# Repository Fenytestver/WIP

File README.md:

# Sump Pit Sensor & Remote monitoring

## Overview
to stop tracking local onfiguration files, run this git command in SumpPitSensorProject/src/:
git update-index --skip-worktree localsettings.h

## Project structure

SumpPitSensorProject	// project root
	lib					// libraries
		sumppitmodel	// main business logic implementation
	src					// main, runnable files
	test				// test code
## Links
http://particle.io - Particle.io

http://bitbucket.com - Version control (git)

https://www.sourcetreeapp.com/ - Win/Mac client for Git

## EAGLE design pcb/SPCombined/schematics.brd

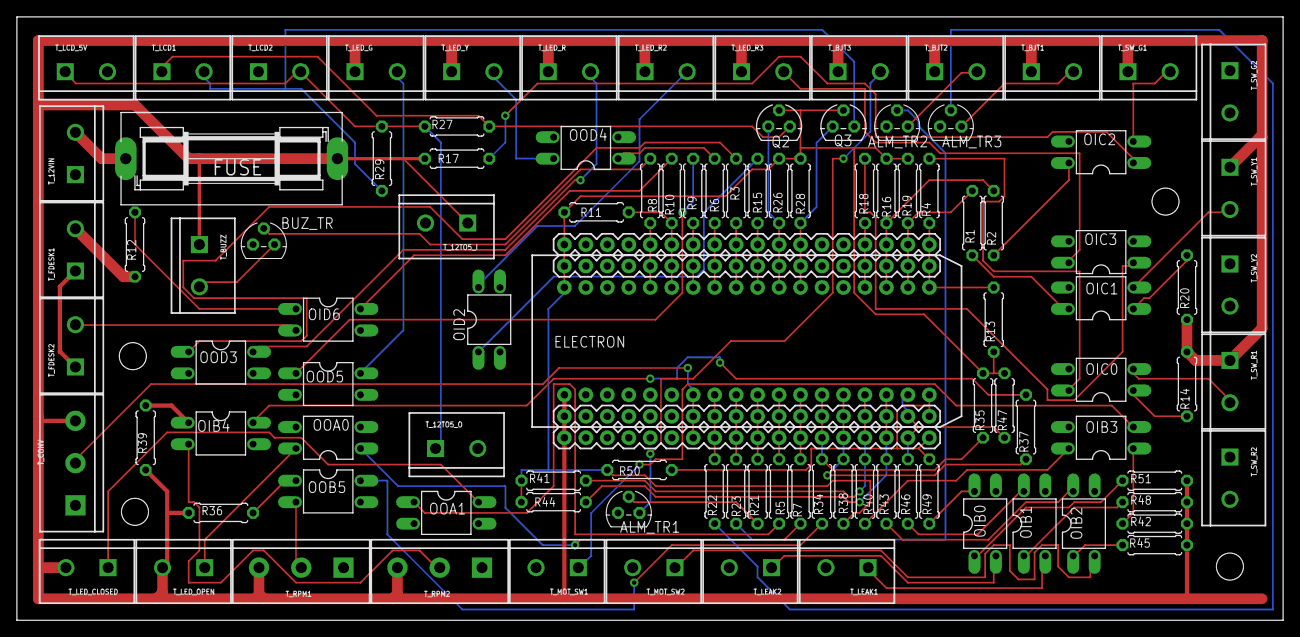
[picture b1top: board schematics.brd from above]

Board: 2 copper layers, 149.8 x 71.4 mm, 102 parts (0 on the bottom side), 85 nets.

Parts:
ALM_TR1, ALM_TR2, ALM_TR3: 2N3904; TO92
BUZ_TR: 2N3904; TO92
ELECTRON: ELECTRONDUALROW; ELECTRON_DUAL-ROW
FUSE: SH25
OIB0, OIB1, OIB2, OIB3, OIB4: PC817; DIL04
OIC0, OIC1, OIC2, OIC3: PC817; DIL04
OID2, OID6: PC817; DIL04
OOA0, OOA1: PC817; DIL04
OOB5: PC817; DIL04
OOD3, OOD4, OOD5: PC817; DIL04
Q2, Q3: TO-92
R1, R2, R3, R4, R5, R6, R7, R9, R10, R15, R18, R34, R37, R40, R43, R46, R49: 220; 0207/7
R8, R21, R22, R23: 2.2k; 0207/7
R11, R13, R16, R19, R26, R27, R28, R29, R35, R38, R41, R44, R47, R50: 10k; 0207/7
R12, R14, R17, R20, R36, R39, R42, R45, R48, R51: 1k; 0207/7
T_12TO5_I, T_12TO5_O, T_12VIN: SCREWTERMINAL-5MM-2
T_BJT1, T_BJT2, T_BJT3: SCREWTERMINAL-5MM-2
T_BUZZ: SCREWTERMINAL-5MM-2
T_CONV: SCREWTERMINAL-5MM-3
T_FDESK1, T_FDESK2: SCREWTERMINAL-5MM-2
T_LCD1, T_LCD2: SCREWTERMINAL-5MM-2
T_LCD_5V: SCREWTERMINAL-5MM-2
T_LEAK1, T_LEAK2: SCREWTERMINAL-5MM-2
T_LED_CLOSED: SCREWTERMINAL-5MM-2
T_LED_G: SCREWTERMINAL-5MM-2
T_LED_OPEN: SCREWTERMINAL-5MM-2
T_LED_R, T_LED_R2, T_LED_R3: SCREWTERMINAL-5MM-2
T_LED_Y: SCREWTERMINAL-5MM-2
T_MOT_SW1, T_MOT_SW2: SCREWTERMINAL-5MM-2
T_RPM1, T_RPM2: SCREWTERMINAL-5MM-3
T_SW_G1, T_SW_G2: SCREWTERMINAL-5MM-2
T_SW_R1, T_SW_R2: SCREWTERMINAL-5MM-2
T_SW_Y1, T_SW_Y2: SCREWTERMINAL-5MM-2

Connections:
+3V3: ELECTRON.3V3, ELECTRON.55, ELECTRON.91, Q2.2, Q3.2, R11.1, R13.1, R16.1, R19.1, R26.2, R28.2, R35.1, R38.1, R41.1, R44.1, R47.1, R50.1
+5V: R27.2, R29.2, T_12TO5_O.1, T_LCD2.2, T_LCD_5V.1
+12V: ELECTRON.1, ELECTRON.37, ELECTRON.VIN, FUSE.2, R14.1, R17.1, R20.1, R36.1, R39.1, R42.1, R45.1, R48.1, R51.1, T_12TO5_I.1, T_BJT1.1, T_BJT2.1, T_BJT3.1, T_BUZZ.1, T_CONV.3, T_LED_CLOSED.2, T_LED_G.1, T_LED_OPEN.2, T_LED_R.1, T_LED_R2.1, T_LED_R3.1, T_LED_Y.1, T_RPM1.3, T_RPM2.3, T_SW_G1.1, T_SW_R1.1, T_SW_Y1.1
+12VIN: FUSE.1, T_12VIN.2
FDESK_12V: R12.1, T_FDESK1.2
FDESK_GND: T_FDESK1.1, T_FDESK2.1
GND: ALM_TR1.3, ALM_TR2.3, ALM_TR3.3, BUZ_TR.3, ELECTRON.2, ELECTRON.38, ELECTRON.58, ELECTRON.94, ELECTRON.GND, ELECTRON.GND@2, OIB0.3, OIB1.3, OIB2.3, OIB3.3, OIB4.3, OIC0.3, OIC1.3, OIC2.3, OIC3.2, OIC3.3, OID2.2, OID2.3, OID6.3, OOA0.2, OOA0.3, OOA1.2, OOA1.3, OOB5.3, OOD3.2, OOD3.3, OOD4.2, OOD4.3, OOD5.2, OOD5.3, T_12TO5_I.2, T_12TO5_O.2, T_12VIN.1, T_CONV.1, T_LCD2.1, T_LCD_5V.2, T_LEAK1.2, T_LEAK2.2, T_MOT_SW1.2, T_MOT_SW2.2, T_RPM1.1, T_RPM2.1, T_SW_G2.1, T_SW_G2.2, T_SW_R2.1, T_SW_R2.2, T_SW_Y2.1, T_SW_Y2.2
INA_LVL: ELECTRON.7, ELECTRON.43, ELECTRON.A5, T_CONV.2
IN_FLO_VCC: OID6.2, T_FDESK2.2
IN_LEA1: OIB1.2, T_LEAK1.1
IN_LEA2: OIB0.2, T_LEAK2.1
IN_MOT1: OIB3.2, T_MOT_SW1.1
IN_MOT2: OIB2.2, T_MOT_SW2.1
IN_RPM1: OOB5.2, T_RPM1.2
IN_RPM2: OIB4.2, T_RPM2.2
IN_SWG: OIC2.2, T_SW_G1.2
IN_SWR: OIC0.2, T_SW_R1.2
IN_SWY: OIC1.2, T_SW_Y1.2
unnamed: OOD3.1, R3.2
unnamed: OIC1.1, R20.2
unnamed: OOD4.1, R6.2
unnamed: OIC2.1, R17.2
unnamed: OOD5.1, R9.2
unnamed: BUZ_TR.2, R8.1
unnamed: BUZ_TR.1, T_BUZZ.2
unnamed: OID2.1, R15.2
unnamed: OIC0.1, R14.2
unnamed: OID6.1, R12.2
unnamed: OOA1.1, R5.2
unnamed: OID6.4, R10.1
unnamed: OIC0.4, R4.1
unnamed: OIC3.1, R18.2
unnamed: OOA0.1, R7.2
unnamed: OIC2.4, R2.1
unnamed: OIC1.4, R1.1
unnamed: ALM_TR1.2, R21.1
unnamed: ALM_TR3.2, R22.1
unnamed: ALM_TR2.2, R23.2
unnamed: OOB5.1, R36.2
unnamed: OOB5.4, R34.1
unnamed: OIB4.1, R39.2
unnamed: OIB4.4, R37.1
unnamed: OIB3.1, R42.2
unnamed: OIB3.4, R40.1
unnamed: OIB2.1, R45.2
unnamed: OIB2.4, R43.1
unnamed: OIB1.1, R48.2
unnamed: OIB1.4, R46.1
unnamed: OIB0.1, R51.2
unnamed: OIB0.4, R49.1
OUT_BJT1: ALM_TR3.1, T_BJT1.2
OUT_BJT2: ALM_TR2.1, T_BJT2.2
OUT_BJT3: ALM_TR1.1, T_BJT3.2
OUT_LCLO: OOA1.4, T_LED_CLOSED.1
OUT_LG: OOD5.4, T_LED_G.2
OUT_LOPE: OOA0.4, T_LED_OPEN.1
OUT_LR: OOD3.4, T_LED_R.2
OUT_LR2: OID2.4, T_LED_R2.2
OUT_LR3: OIC3.4, T_LED_R3.2
OUT_LY: OOD4.4, T_LED_Y.2
PIN_BJT1: ELECTRON.9, ELECTRON.45, ELECTRON.A3, R23.1
PIN_BJT2: ELECTRON.8, ELECTRON.44, ELECTRON.A4, R22.2
PIN_BUZ: ELECTRON.59, ELECTRON.95, ELECTRON.D7, R8.2
PIN_FLO: ELECTRON.60, ELECTRON.96, ELECTRON.D6, R10.2, R11.2
PIN_LCLO: ELECTRON.11, ELECTRON.47, ELECTRON.A1, R5.1
PIN_LEA1: ELECTRON.17, ELECTRON.53, ELECTRON.B1, R46.2, R47.2
PIN_LEA2: ELECTRON.18, ELECTRON.54, ELECTRON.B0, R49.2, R50.2
PIN_LG: ELECTRON.61, ELECTRON.97, ELECTRON.D5, R9.1
PIN_LOPE: ELECTRON.12, ELECTRON.48, ELECTRON.A0, R7.1
PIN_LR: ELECTRON.63, ELECTRON.99, ELECTRON.D3, R3.1
PIN_LR2: ELECTRON.64, ELECTRON.100, ELECTRON.D2, R15.1
PIN_LR3: ELECTRON.69, ELECTRON.105, ELECTRON.C3, R18.1
PIN_LY: ELECTRON.62, ELECTRON.98, ELECTRON.D4, R6.1
PIN_MOT1: ELECTRON.15, ELECTRON.51, ELECTRON.B3, R40.2, R41.2
PIN_MOT2: ELECTRON.16, ELECTRON.52, ELECTRON.B2, R43.2, R44.2
PIN_RPM1: ELECTRON.13, ELECTRON.49, ELECTRON.B5, R34.2, R35.2
PIN_RPM2: ELECTRON.14, ELECTRON.50, ELECTRON.B4, R37.2, R38.2
PIN_SCL: ELECTRON.65, ELECTRON.101, ELECTRON.D1, Q2.1, R26.1
PIN_SDA: ELECTRON.66, ELECTRON.102, ELECTRON.D0, Q3.1, R28.1
PIN_SIREN: ELECTRON.10, ELECTRON.46, ELECTRON.A2, R21.2
PIN_SWG: ELECTRON.70, ELECTRON.106, ELECTRON.C2, R2.2, R16.2
PIN_SWR: ELECTRON.72, ELECTRON.108, ELECTRON.C0, R4.2, R13.2
PIN_SWY: ELECTRON.71, ELECTRON.107, ELECTRON.C1, R1.2, R19.2
SCL: Q2.3, R27.1, T_LCD1.1
SDA: Q3.3, R29.1, T_LCD1.2

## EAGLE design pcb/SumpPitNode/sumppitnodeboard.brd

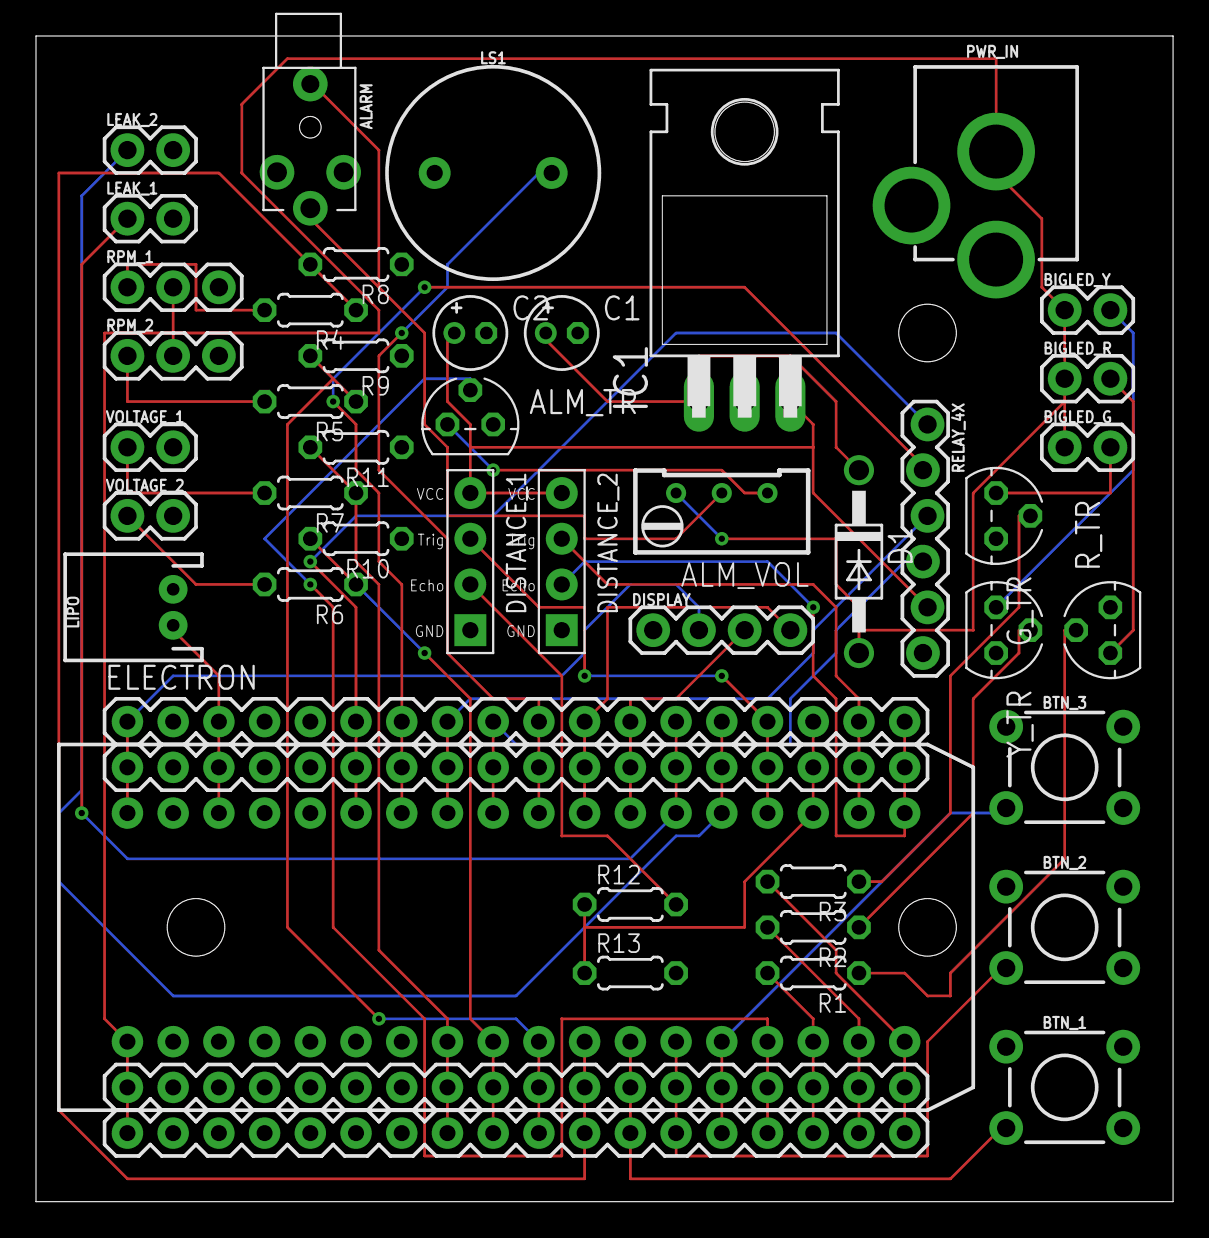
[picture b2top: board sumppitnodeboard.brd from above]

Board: 2 copper layers, 63.2 x 64.8 mm, 43 parts (0 on the bottom side), 43 nets.

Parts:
ALARM: STEREOJACK2.5MM_STEREOJACK2.5MM
ALM_TR: 2N3904; TO92
ALM_VOL: 10k; RTRIM64W
BIGLED_G: 1X02
BIGLED_R: 1X02
BIGLED_Y: 1X02
BTN_1, BTN_2, BTN_3: MOMENTARY-SWITCH-SPST-PTH-6.0MM; TACTILE_SWITCH_PTH_6.0MM
C1, C2: E1,8-4
D1: 1N4004; DO41-10
DISPLAY: 1X04
DISTANCE_1, DISTANCE_2: HC-SR04; HC-SR04_FOOTPRINT
ELECTRON: ELECTRONDUALROW; ELECTRON_DUAL-ROW
G_TR: 2N3904; TO92
IC1: 7805T; TO220H
LEAK_1, LEAK_2: 1X02
LIPO: JST-2-PTH
LS1: BUZZER-PTH; BUZZER-12MM
PWR_IN: POWER_JACK; POWER_JACK_PTH
R1, R2, R3: 51; 0204/5
R4, R5, R6, R7, R8, R9, R10, R11: 0204/5
R12, R13: 470; 0204/5
RELAY_4X: 1X06_LOCK
RPM_1, RPM_2: 1X03
R_TR: 2N3904; TO92
VOLTAGE_1, VOLTAGE_2: 1X02
Y_TR: 2N3904; TO92

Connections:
3V3: DISPLAY.2, ELECTRON.3V3, ELECTRON.55, ELECTRON.91
GND: ALARM.RING1, ALM_TR.1, BTN_1.1, BTN_2.1, BTN_3.1, C1.-, C2.-, DISPLAY.1, DISTANCE_1.GND, DISTANCE_2.GND, ELECTRON.2, ELECTRON.38, ELECTRON.58, ELECTRON.94, ELECTRON.GND, ELECTRON.GND@2, G_TR.1, IC1.2, LEAK_1.2, LEAK_2.2, LIPO.2, LS1.-, PWR_IN.PWR, R8.1, R9.1, R10.1, R11.1, R13.2, RELAY_4X.6, RPM_1.3, RPM_2.3, R_TR.1, VOLTAGE_1.2, VOLTAGE_2.2, Y_TR.1
unnamed: ALARM.SHIELD, ALARM.TIP, ALM_VOL.2
unnamed: ALM_TR.3, ALM_VOL.1
unnamed: ALM_TR.2, ELECTRON.15, ELECTRON.51, ELECTRON.B3
unnamed: R1.1, R_TR.2
unnamed: ELECTRON.17, ELECTRON.53, ELECTRON.B1, R2.2
unnamed: ELECTRON.18, ELECTRON.54, ELECTRON.B0, R3.2
unnamed: BTN_3.3, ELECTRON.14, ELECTRON.50, ELECTRON.B4
unnamed: ELECTRON.57, ELECTRON.93, ELECTRON.VBAT, LIPO.1
unnamed: BTN_2.3, ELECTRON.13, ELECTRON.49, ELECTRON.B5
unnamed: BTN_1.3, ELECTRON.12, ELECTRON.48, ELECTRON.A0
unnamed: DISPLAY.3, ELECTRON.66, ELECTRON.102, ELECTRON.D0
unnamed: DISPLAY.4, ELECTRON.65, ELECTRON.101, ELECTRON.D1
unnamed: BIGLED_G.2, G_TR.3
unnamed: DISTANCE_1.ECHO, R12.2
unnamed: DISTANCE_2.ECHO, ELECTRON.72, ELECTRON.108, ELECTRON.C0
unnamed: DISTANCE_2.TRIG, ELECTRON.71, ELECTRON.107, ELECTRON.C1
unnamed: DISTANCE_1.TRIG, ELECTRON.69, ELECTRON.105, ELECTRON.C3
unnamed: C1.+, D1.C, IC1.1
unnamed: ELECTRON.16, ELECTRON.52, ELECTRON.B2, R1.2
unnamed: R2.1, Y_TR.2
unnamed: G_TR.2, R3.1
unnamed: ELECTRON.64, ELECTRON.100, ELECTRON.D2, LS1.+
unnamed: ELECTRON.67, ELECTRON.103, ELECTRON.C5, LEAK_1.1
unnamed: R6.2, VOLTAGE_2.1
unnamed: R5.2, RPM_2.1
unnamed: R4.2, RPM_1.1
unnamed: R7.2, VOLTAGE_1.1
unnamed: ELECTRON.70, ELECTRON.106, ELECTRON.C2, R12.1, R13.1
unnamed: BIGLED_Y.2, Y_TR.3
unnamed: BIGLED_R.2, R_TR.3
unnamed: ELECTRON.68, ELECTRON.104, ELECTRON.C4, LEAK_2.1
unnamed: C2.+, DISTANCE_1.VCC, DISTANCE_2.VCC, IC1.3, RELAY_4X.5
unnamed: ELECTRON.63, ELECTRON.99, ELECTRON.D3, RELAY_4X.4
unnamed: ELECTRON.62, ELECTRON.98, ELECTRON.D4, RELAY_4X.3
unnamed: ELECTRON.61, ELECTRON.97, ELECTRON.D5, RELAY_4X.2
unnamed: ELECTRON.60, ELECTRON.96, ELECTRON.D6, RELAY_4X.1
PIN_RPM_1: ELECTRON.11, ELECTRON.47, ELECTRON.A1, R4.1, R8.2
PIN_RPM_2: ELECTRON.10, ELECTRON.46, ELECTRON.A2, R5.1, R9.2
PIN_VOLT_1: ELECTRON.8, ELECTRON.44, ELECTRON.A4, R7.1, R11.2
PIN_VOLT_2: ELECTRON.9, ELECTRON.45, ELECTRON.A3, R6.1, R10.2
VCC_1: ALM_VOL.3, BIGLED_G.1, BIGLED_R.1, BIGLED_Y.1, D1.A, ELECTRON.1, ELECTRON.37, ELECTRON.VIN, PWR_IN.GND, RPM_1.2, RPM_2.2

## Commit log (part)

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2018-09-14 Initial commit, add model base: skeleton.cpp Add stub implementation for a few classes. Add demo arduino code.
2018-09-15 Add updateable. Add snoozeable siren. Fix build.
2018-09-15 Add a few lines to readme
2018-09-15 Remove arduino dependency from library code.
2018-09-15 Add gradle native build.
2018-09-15 add gitignore
2018-09-15 update gitignore
2018-09-15 remove .gradle contents
2018-09-16 Move files to use gradle build for tests. Remove tests, they break the build with Arduino IDE, need to extract to separate folder.
2018-09-16 Create codeblocks project. Create class headers/implementation for model. Start impementing test base that initializes all stub implmentation for testing.
2018-09-17 imlement initialization to armed by default. implement leak and water level detection and starting alarm in armed mode. implement first test.
2018-09-17 Add check for disarming during alarm.
2018-09-17 Add timer class. Fix project.
2018-09-17 Ignore build dirs.
2018-09-17 Add system time. Start implementing motor start detection with spinup timeout.
2018-09-18 README.md edited online with Bitbucket
2018-09-19 Reorganize tests to test main, test base class, test case implementations with a complete node is set up in stub mode. One of the tests still fails.
2018-09-20 fix pump test
2018-09-21 Create multipump, replace it in tests. remove test_engine, its contents was moved to other classes.
2018-09-22 Rename p1,p2 to subPump1, subPump2
2018-09-22 Cleanup multipump test.
2018-09-22 add no water level constant, project file update.
2018-09-23 Implement mltiwater sensor. Implement tests.
2018-09-23 Start creating particle build.
2018-09-23 Create particle io project, lib. Move sources, update codeblocks project.
2018-09-23 ignore binaries from particle.io
2018-09-23 Reorganize, update readme.
2018-09-24 Fix tests and array allocation. Fix logging style.
2018-09-24 Save project. Add log for stub siren.
2018-09-24 Add pinmap proposal
2018-09-26 update analog to digital
2018-09-27 Connect more wires. distance to interrupt pins. i2c display 5v voltage regulator for distance sensor. add resistors for leds.
2018-09-28 Connect buzzer.
2018-09-28 connect rpm, voltage with voltage dividers (12v->2.8v)
2018-09-28 Fix, add multiple vcc, create base sch.
2018-09-30 Generate board, connect more sensors.
2018-09-30 Remove multiwater sensor.
2018-09-30 add shutoffvalve
2018-09-30 Save prj.
2018-09-30 Add relay 4.
2018-09-30 Place 4relay.
2018-09-30 Add power, update routing.
2018-10-01 fix endline.
2018-10-02 Reconnect leak sensors without pulldown.
2018-10-02 Save (was missing).
2018-10-02 Add display constants. Add empty class. Add a few small tests (demos).
2018-10-05 Removed turning logic from pump. Moved status check inside. Update tests, remove pump unit test, because it makes no sense anymore. Voltage sensors are changed to simulate pump on/off states.
2018-10-05 re-enable tests.
2018-10-05 Fix assert flag.
2018-10-06 Fix water flood sensor, enable pullup.
2018-10-06 Implement buttons, long, short press. Implement siren, buzzer.
2018-10-06 Implement shut off valve that controls a relay pin.
2018-10-06 no message
2018-10-06 Add water level sensor with stub config.
2018-10-07 Save project.
2018-10-13 Detect low water. Fix water level instability problem by adding a water variance constant. Extend failure and normal operation tests.
2018-10-13 Fix pump rpm instability by margin constant. Extend tests.
2018-10-13 Save.
2018-10-14 Move button listeners to node.
2018-10-14 Remove from arduino code.
2018-10-15 Implement missing real sensors with stub logic. Initialize and run the whole code.
2018-10-18 Restructure led driver folders.
2018-10-18 Implement basic display control.
2018-10-18 Display welcome message.
2018-10-22 Save
2018-10-23 Implement a few cases for displaying data, doesnt work yet.
2018-10-30 display fixin, still memory leak somewhere.
2018-11-04 Fix display.
2018-11-19 Sample test run.
2018-11-19 Fix null chars.
2018-11-29 Add a lot of everything. Implement display logic partly, stub display, refactor, cleanup, some extra tests.
2018-11-29 save project
2018-12-29 Add environment.
2018-12-30 Replace LCD driver.
2018-12-30 revert config to photon
2019-01-02 replace ultrasonic with analog read. disable some sensors with no=pin definition. fix lcd.
2019-01-02 re-organize application.ino, force platform selection.
2019-01-02 disable voltage add debug to serial
2019-01-02 add analog water level support on A0. connect potentiometer to gnd, a0, vcc(3v3)
2019-01-03 Shorter water alert message.
2019-01-03 fix order of lcd lines.
2019-01-03 Create local settings file.
2019-01-03 Ignore localsettings.h
2019-01-03 Move localsettings out of src
2019-01-03 Ignor src/localsettings.h
2019-01-03 Reorganize pins. Push some data to cloud. Merge leak sensors to one class.
2019-01-05 Fix too long lines on local view. Fix pump1,2 ON/OFF state (was based on rpm > 0, which is wrong). Remove pin definitions from photon platform. Reduce loop delay to 50. Replace analogread in voltage 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
2019-01-05 Fix "water alarm" shown with anything.
2019-01-05 Fix button, siren, buzzer pin setup.
2019-01-05 Fix hardware status led setup.
2019-01-05 Add cloud function to control state.
2019-01-05 Do not deactivate shut off valve from node. Ever.
2019-01-06 Set shorter names on functions and variables.
2019-01-06 Google Fi sample project. Set keepalive for 3rd party sim.
2019-01-06 Setup rpm sensor pins. Add interrupt a rate counting. Add sample arduino wave generator. Available pins: https://docs.particle.io/reference/device-os/firmware/photon/#interrupts
2019-01-07 Add technical, critical 0/1 to sync. Send 0/1 for leak. Send rssi, signal bars.
2019-01-07 Impleent dual channel square wave generator.
2019-01-07 Fix maintenance mode display.
2019-01-07 Make button long press configurable.
2019-01-08 More precise square wave calculation.
2019-01-08 Fix rpm generator.
2019-01-08 Set RPM meassure time to .5 sec. Read analog signal when potmeter connected.
2019-01-09 Fix non configurable long press time. Fix test runner.
2019-01-09 Fix button parameter order.
2019-01-09 Add new particle functions: - trigger update immediately - get lcd text
2019-01-10 Turn off shutoff valve when turned off on another device. Add valve value to state. Make shut off valve message non-private.
2019-01-11 Add webhook readme
2019-01-11 Fix format.
2019-01-11 Add more details to webhook doc.
2019-01-11 Add float switch.
2019-01-11 Fix newline in one line message.
2019-01-11 Refactor.
2019-01-12 Implement water rising while pumps are on error.
2019-01-12 Replace water low alert with pump failed to turn off (pump has to be running).
2019-01-12 Fix RPM deviation error and message.
2019-01-12 Add 3rd leak pin.
2019-01-12 Fix water low test: simulate pump still running.
2019-01-12 Implement scroll.
2019-01-12 Implement manual mode with connecting text.
2019-01-12 Manual mode with status text.
2019-01-12 Remove delays.
2019-01-13 Configurable water low/high values (analogRead, inches)
2019-01-13 Add remote eeprom config for critical water percentage.
2019-01-13 Fix json format.
2019-01-13 Show some of the technical errors during a critical alarm.
2019-01-13 Update webhook doc.
2019-01-13 Update webhook doc. Add status name, add text widget.
2019-01-13 Add lcd display webhook styling.
2019-01-15 Update metric html howto.
2019-01-20 Render maintenance mode with armed rendering, but without a siren and shutoff valve.
2019-01-20 Add sensor node readme. Fix variables.
2019-01-20 Format readme.
2019-01-20 Fix typos in doc.
2019-01-20 Implement 1Hz alarm.
2019-01-20 Implement snooze.
2019-01-20 Implement button snooze.
2019-01-21 Fix waterLowIn result from function. Make leak technical.
2019-01-21 Implement simple automatic calibration by pressing 3 buttons.
2019-01-21 Check if system is on battery. Trigger technical.
2019-01-21 Implement list of critical alert that trigger water shutoff.
2019-01-23 Remove SPN_WATER_VARIANCE from calibration.
2019-01-23 Fix water variance not calculated correctly.
2019-01-24 Turn off siren while pressing disarm.
2019-01-24 Improve sync timing. Add new max sync time constants for technical/critical alarm.
2019-01-25 Multiply RPM by 60 to get per minute instead of per second.
2019-01-25 Fix RPM calculation. Measure time between 2 'R'.
2019-01-25 Improve squarewave generator, more accurate.
2019-01-26 Fix system voltage sensor problems. Fix docs for warning message. Fix tests: - parameter - warnings - leak sensor turned to a warning, not ringing any alarms - water level low alarm only started when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
2019-01-26 Update RPM calculation, minimum 60RPM.
2019-01-26 Improve calibartion display. More accurate inch calculation.
2019-01-26 Move lib to dedicated folder. Increment version.
2019-01-27 Implement actuator base. Fix shutoff valve sync. Send current mode on mode change.
2019-01-27 Implement open/closed status leds.
2019-01-27 Implement alarm module project base.
2019-01-27 Fix snooze.
2019-01-27 Add float switch to shutoff alerts. Increment model version to 0.0.3. Depend on it. Parse error code, only start siren for shutoff level alerts (CriticalB). Implement alarm lights with some extras.
2019-01-27 Fix too fast timing.
2019-01-27 Fix: reset alarm timer when no alarm present.
2019-01-27 implement remote snooze.
2019-01-28 Remove blinking red led. Add clear eeprom code.
2019-01-28 Implement sensig shutoff valve with 5sec timeout to be unknown. Request status update after reboot.
2019-01-29 Implement multinode support.
2019-01-29 Beep when snoozed.
2019-01-29 Fix red led on disarmed on sensor.
2019-01-30 Add helper scripts to copy deps to place. And a cleanup script.
2019-01-30 Add model copy to gitignore.
2019-01-31 Depend on 0.0.3 from SPN.
2019-01-31 Fix sensor node led colors. Fix alarm does not stop after critical->technical.
2019-01-31 Implement optional LCD, put definition in local settings to disable screen: #define DISPLAY_I2C_ADDR 0x00
2019-02-23 Upload FW.
2019-03-26 PCB size 2mm margin.
2019-03-27 Save autoroute state.
2019-03-27 Add libs.
2019-03-28 Rereroute.
2019-03-30 V0.2 no names/values on silkscreen. V0.2.1 with names/values on silkscreen. can job updated to have names/values on silkscreen.
2019-03-30 And again save cam.
2019-03-31 High res img.
2019-05-19 detect anomalies at shutoff node (expected and actual shutoff values). detect power issues at shutoff node. publish anomalies from shutoff node. publish pupmp count from sensor node when change.
2019-05-23 Helyes PIN kiosztas (PCB szerint)
2019-05-31 Send periodic status. Red leds respect snooze. Red led off in maintenance. Power detector state in actuator status report. Pump individual state in sensor status updates.
2019-06-11 Bump lib version.
2019-06-14 Fix timer.
2019-06-14 Move keep alive packet to main loop.
2019-06-14 Remove 1.0 bin.
2019-06-15 Fix power and uptime. Fix anomaly reporting (2 seconds timeout). Add more logs.
2019-06-17 Fix critical alert during maintenance on actuator and alarm nodes.
2019-06-18 Add log to alarm node.
2019-06-21 Use PRIVATE when publishing. Use MY_DEVINCES when subscribing. Add some logs.
2019-06-21 Use private in impl.ino.
2019-06-26 Bump model version. Fix red led timing.
2019-06-29 Force critial in case of an anomaly.
2019-06-29 Add clusters.
2019-06-29 Read cluster at boot.
2019-06-29 Fix scope of shutoff publish. Move to c cluster prefix. Add logs. Fix logs for button.
2019-06-30 Turn off google fi settings.
2019-07-11 Json and Particle libraries
2019-07-12 Delete 340039000d51363034323832_ec_new.der
    not needed
2019-07-12 Delete 340039000d51363034323832_ec_new.pem
    not needed
2019-07-12 Delete 340039000d51363034323832_ec_new.pub.pem
    not needed
2019-07-12 Delete 450028001550483553353620_ec_new.der
    not needed
2019-07-12 Delete 450028001550483553353620_ec_new.pub.pem
    not needed
2019-07-12 Delete backup_ec_340039000d51363034323832_ec_new.der
    not needed
2019-07-12 Delete backup_ec_340039000d51363034323832_ec_new.pub.pem
    not needed
2019-07-12 Delete backup_ec_450028001550483553353620_ec_new.der
    not needed
2019-07-12 not needed files
2019-07-12 Add local setting example
2019-07-12 inital comit
2019-07-12 Set KeepAliveTimer to 5 min.

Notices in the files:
parts and their libraries:
SparkFun-Connectors: Licensing: Creative Commons ShareAlike 4.0 International - https://creativecommons.org/licenses/by-sa/4.0
